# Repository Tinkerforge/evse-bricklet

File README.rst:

EVSE Bricklet
=============

This Bricklet together with the ESP32 Brick the NFC Bricklet and the
RS485 Bricklet form the hardware used in the WARP Charger.

See https://www.warp-charger.com/warp1.html for more details.

This repository contains the firmware source code and the hardware design
files. The documentation generator configs can be found at
https://github.com/Tinkerforge/generators

.. BEGIN WARP REPOSITORIES (managed block, generated from esp32-firmware/repo_overview.rst - do not edit by hand, run update_repo_overview.py instead)

WARP Repositories
-----------------

This is an overview of all repositories that make up the WARP Charger and
WARP Energy Manager ecosystem.

Please report **any** issue concerning WARP hard- or software in the
`esp32-firmware`_ repository, no matter which repository it originates from.

Software
~~~~~~~~

- `esp32-firmware`_ - Source code of the ESP32 firmware shared between all WARP Chargers and Energy Managers

Libraries used by the firmware:

- `tfjson`_ - SAX style JSON serializer and deserializer
- `tfnetwork`_ - Modbus TCP server and client implementation
- `tfocpp`_ - OCPP 1.6 implementation
- `tftools`_ - Miscellaneous tools and helpers

Remote access:

- `esp32-remote-access`_ - Source code of the my.warp-charger.com remote access server

Documentation, tools and integrations:

- `warp-charger`_ - Source code of (docs.)warp-charger.com and the printed manual, released firmwares, datasheets and documents, as well as some tools and hardware design files
- `api.warp-charger.com`_ - Serves APIs that are used by WARP Chargers to obtain relevant public information like day ahead prices
- `vislog.warp-charger.com`_ - Visualizes WARP Charger logs and EVSE debug protocols
- `dbus-warp-charger`_ - Integrates WARP Chargers into a Victron Energy Venus OS device (e.g. Cerbo GX)

WARP Charger Hardware
~~~~~~~~~~~~~~~~~~~~~~

WARP4 Charger
"""""""""""""

*Current charger generation.*

- `warp-esp32-ethernet-v2-brick`_ - Hardware design files of the WARP ESP32 Ethernet Brick 2.0
- `warp-esp32-ethernet-v2-co-bricklet`_ - Firmware source code of the WARP ESP32 Ethernet 2.0 Co Bricklet (co-processor)
- `evse-v4-bricklet`_ - Hardware design files of the EVSE 4.0 Bricklet (firmware shared with the EVSE 2.0 Bricklet)
- `nfc-bricklet`_ - Firmware source code and hardware design files of the NFC Bricklet

WARP3 Charger
"""""""""""""

- `warp-esp32-ethernet-brick`_ - Hardware design files of the WARP ESP32 Ethernet Brick
- `evse-v3-bricklet`_ - Hardware design files of the EVSE 3.0 Bricklet (firmware shared with the EVSE 2.0 Bricklet)
- `nfc-bricklet`_ - Firmware source code and hardware design files of the NFC Bricklet

WARP2 Charger
"""""""""""""

- `esp32-ethernet-brick`_ - Hardware design files of the ESP32 Ethernet Brick
- `evse-v2-bricklet`_ - Firmware source code and hardware design files of the EVSE 2.0 Bricklet
- `nfc-bricklet`_ - Firmware source code and hardware design files of the NFC Bricklet

WARP1 Charger
"""""""""""""

- `esp32-brick`_ - Hardware design files of the ESP32 Brick
- `evse-bricklet`_ - Firmware source code and hardware design files of the EVSE Bricklet
- `rs485-bricklet`_ - Firmware source code and hardware design files of the RS485 Bricklet

WARP Energy Manager Hardware
~~~~~~~~~~~~~~~~~~~~~~~~~~~~~~

WARP Energy Manager 2.0
"""""""""""""""""""""""

*Current energy manager generation.*

- `esp32-ethernet-brick`_ - Hardware design files of the ESP32 Ethernet Brick
- `warp-energy-manager-v2-bricklet`_ - Firmware source code and hardware design files of the WARP Energy Manager 2.0 Bricklet
- `warp-front-panel-bricklet`_ - Firmware source code and hardware design files of the WARP Front Panel Bricklet

WARP Energy Manager 1.0
"""""""""""""""""""""""

- `esp32-ethernet-brick`_ - Hardware design files of the ESP32 Ethernet Brick
- `warp-energy-manager-bricklet`_ - Firmware source code and hardware design files of the WARP Energy Manager Bricklet

Forked/patched projects
~~~~~~~~~~~~~~~~~~~~~~~~~

- `arduino-esp32`_
- `esp32-arduino-libs`_
- `WireGuard-ESP32-Arduino`_

.. Link targets: One definition per repository, keep in sync with the lists above.

.. _esp32-firmware: https://github.com/Tinkerforge/esp32-firmware
.. _tfjson: https://github.com/Tinkerforge/tfjson
.. _tfnetwork: https://github.com/Tinkerforge/tfnetwork
.. _tfocpp: https://github.com/Tinkerforge/tfocpp
.. _tftools: https://github.com/Tinkerforge/tftools
.. _esp32-remote-access: https://github.com/Tinkerforge/esp32-remote-access
.. _warp-charger: https://github.com/Tinkerforge/warp-charger
.. _api.warp-charger.com: https://github.com/Tinkerforge/api.warp-charger.com
.. _vislog.warp-charger.com: https://github.com/Tinkerforge/vislog.warp-charger.com
.. _dbus-warp-charger: https://github.com/Tinkerforge/dbus-warp-charger
.. _warp-esp32-ethernet-v2-brick: https://github.com/Tinkerforge/warp-esp32-ethernet-v2-brick
.. _warp-esp32-ethernet-v2-co-bricklet: https://github.com/Tinkerforge/warp-esp32-ethernet-v2-co-bricklet
.. _evse-v4-bricklet: https://github.com/Tinkerforge/evse-v4-bricklet
.. _nfc-bricklet: https://github.com/Tinkerforge/nfc-bricklet
.. _warp-esp32-ethernet-brick: https://github.com/Tinkerforge/warp-esp32-ethernet-brick
.. _evse-v3-bricklet: https://github.com/Tinkerforge/evse-v3-bricklet
.. _esp32-ethernet-brick: https://github.com/Tinkerforge/esp32-ethernet-brick
.. _evse-v2-bricklet: https://github.com/Tinkerforge/evse-v2-bricklet
.. _esp32-brick: https://github.com/Tinkerforge/esp32-brick
.. _evse-bricklet: https://github.com/Tinkerforge/evse-bricklet
.. _rs485-bricklet: https://github.com/Tinkerforge/rs485-bricklet
.. _warp-energy-manager-v2-bricklet: https://github.com/Tinkerforge/warp-energy-manager-v2-bricklet
.. _warp-front-panel-bricklet: https://github.com/Tinkerforge/warp-front-panel-bricklet
.. _warp-energy-manager-bricklet: https://github.com/Tinkerforge/warp-energy-manager-bricklet
.. _arduino-esp32: https://github.com/Tinkerforge/arduino-esp32
.. _esp32-arduino-libs: https://github.com/Tinkerforge/esp32-arduino-libs
.. _WireGuard-ESP32-Arduino: https://github.com/Tinkerforge/WireGuard-ESP32-Arduino

.. END WARP REPOSITORIES

Repository Content
------------------

software/:
 * examples/: Examples for all supported languages
 * build/: Compiled files
 * src/: Source code of firmware
 * Makefile: Makefile to build project

hardware/:
 * Contains KiCad project files and additionally schematics as PDF

datasheets/:
 * Contains datasheets for sensors and complex ICs that are used

Hardware
--------

The hardware is designed with the open source EDA Suite KiCad
(http://www.kicad.org). Before you are able to open the files,
you have to install the Tinkerforge kicad-libraries
(https://github.com/Tinkerforge/kicad-libraries). You can either clone
them directly in hardware/ or clone them in a separate folder and
symlink them into hardware/
(ln -s kicad_path/kicad-libraries project_path/hardware). After that you
can open the .pro file in hardware/ with KiCad and from there view and
modify the schematics and the PCB layout.

Software
--------

If you want to do your own Brick/Bricklet firmware development we highly
recommend that you use our build environment setup script and read the
tutorial (https://www.tinkerforge.com/en/doc/Tutorials/Tutorial_Build_Environment/Tutorial.html).

To compile the C code we recommend you to install the newest GNU Arm Embedded
Toolchain (https://launchpad.net/gcc-arm-embedded/+download).
You also need to install bricklib2 (https://github.com/Tinkerforge/bricklib2).

You can either clone it directly in software/src/ or clone it in a
separate folder and symlink it into software/src/
(ln -s bricklib_path/bricklib2 project_path/software/src/). Finally make sure to
have CMake installed (http://www.cmake.org/cmake/resources/software.html).

After that you can build the firmware by invoking make in software/.
The firmware (.zbin) can then be found in software/build/ and uploaded
with brickv (click button "Flashing" on start screen).

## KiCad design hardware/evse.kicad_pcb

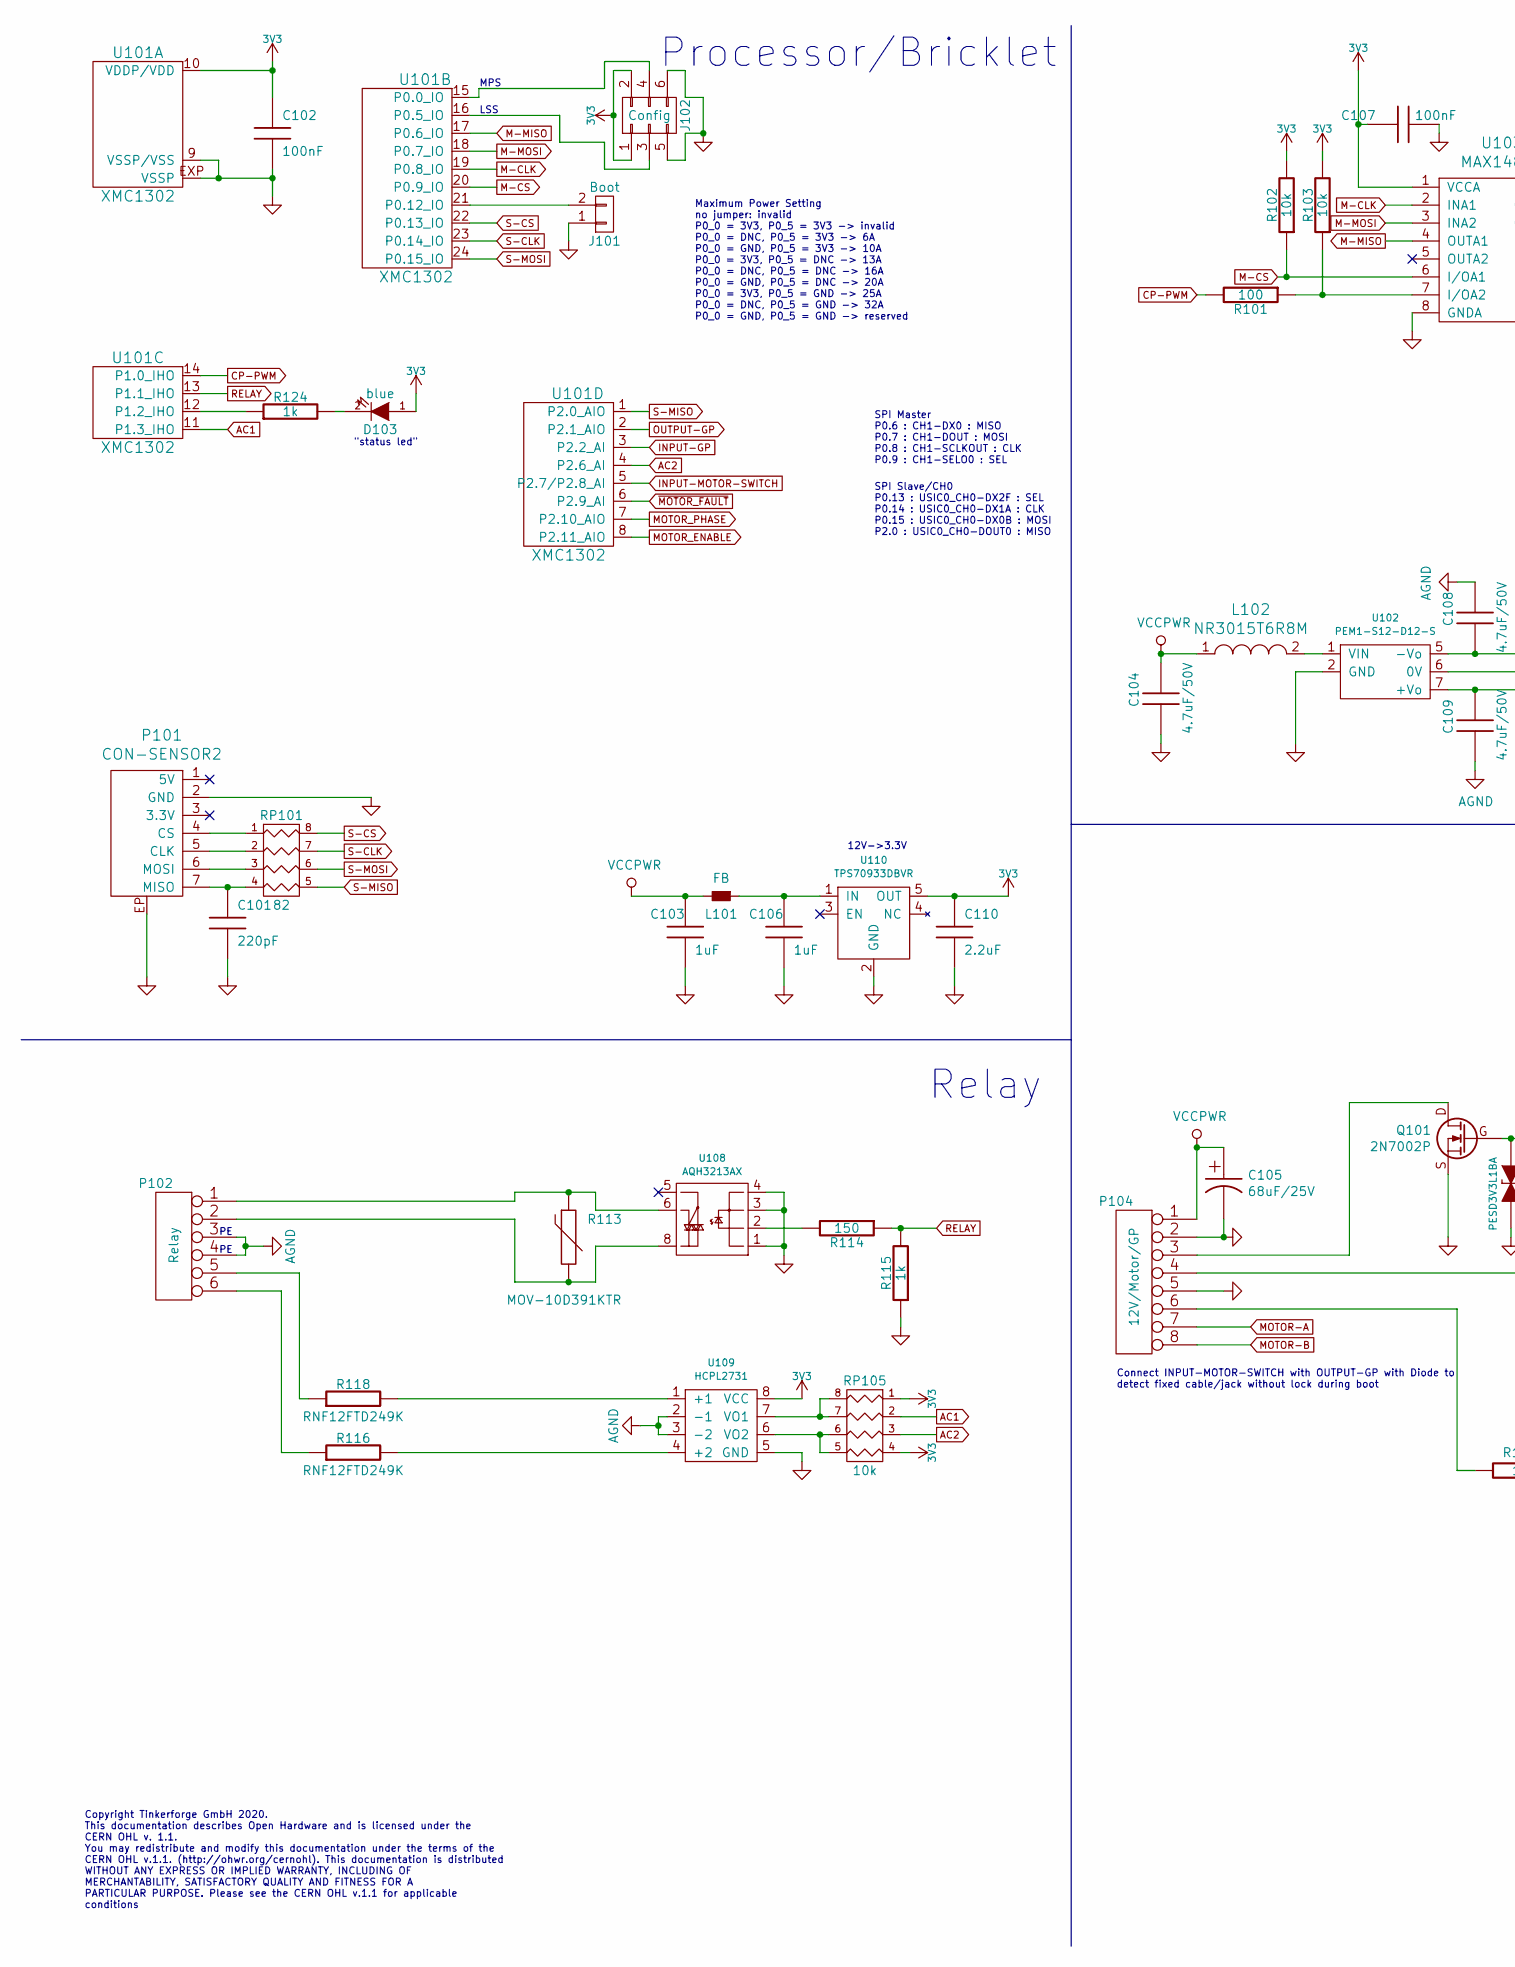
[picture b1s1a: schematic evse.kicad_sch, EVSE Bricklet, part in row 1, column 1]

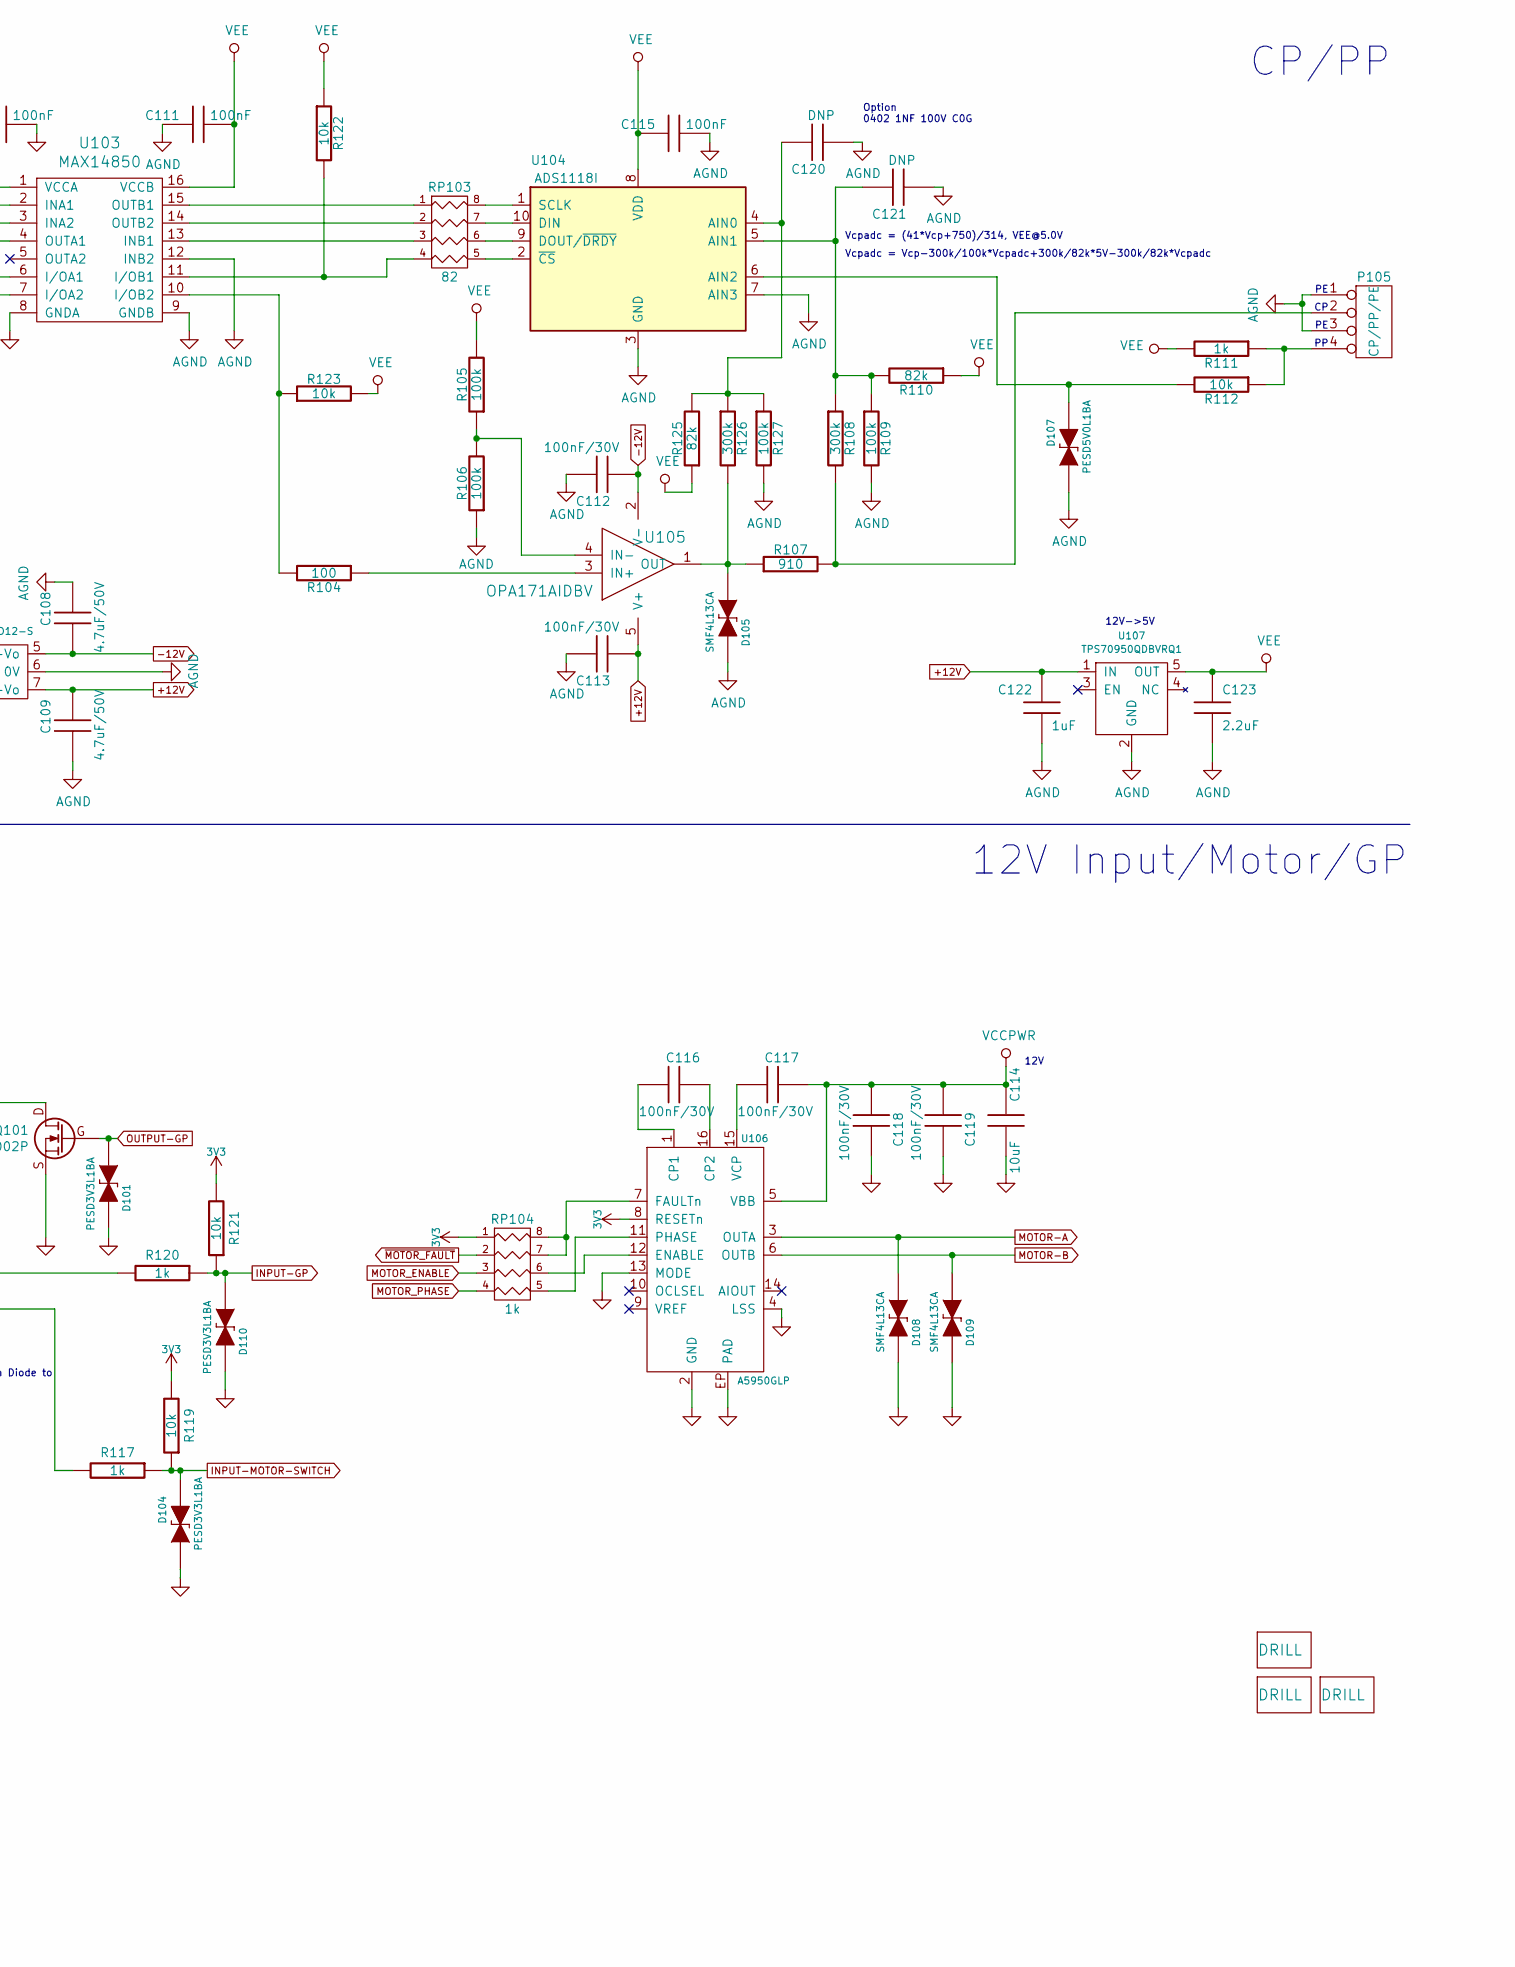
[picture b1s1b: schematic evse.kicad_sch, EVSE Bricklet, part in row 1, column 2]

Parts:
A101, A102, A103: DRILL; DRILL_NP
C101: 220pF; C0402F
C102, C107, C111, C115: 100nF; C0603F
C103, C106, C122: 1uF; C0603F
C104, C108, C109: 4.7uF/50V; C1206
C105: 68uF/25V; ELKO_63
C110, C123: 2.2uF; C0603F
C112, C113, C116, C117, C118, C119: 100nF/30V; C0603F
C114: 10uF; C1206
C120, C121: DNP; C0402F
D101, D104, D110: ‎PESD3V3L1BA; SOD-323
D103: blue; D0603F
D105, D108, D109: SMF4L13CA; SOD-123FL
D107: ‎PESD5V0L1BA; SOD-323
J101: Boot; SolderJumper
J102: Config; Pin_Header_Straight_2x03_127
L101: FB; R0603F
L102: NR3015T6R8M; NR3030
P101: CON-SENSOR2; CON-SENSOR2_180
P102: Relay; OQ_6P_Vertical
P104: 12V/Motor/GP; OQ_8P_Vertical
P105: CP/PP/PE; OQ_4P_Vertical
Q101: 2N7002P; SOT23GDS
R101, R104: 100; R0603F
R102, R103, R112, R119, R121, R122, R123: 10k; R0603F
R105, R106, R109, R127: 100k; R0603F
R107: 910; R0603F
R108, R126: 300k; R0603F
R110, R125: 82k; R0603F
R111, R115, R117, R120, R124: 1k; R0603F
R113: MOV-10D391KTR; VAR_10mm
R114: 150; R0603F
R116, R118: RNF12FTD249K; RNF12
RP101, RP103: 82; 4X0402
RP104: 1k; 4X0603
RP105: 10k; 4X0603
U101: XMC1302; QFN24-4x4mm-0.5mm
U102: PEM1-S12-D12-S; PEM1S
U103: MAX14850; SOIC16
U104: ADS1118I; VSSOP10
U105: OPA171AIDBV; SOT23-5
U106: A5950GLP; TSSOP16_EP
U107: TPS70950QDBVRQ1; SOT23-5
U108: AQH3213AX; AQ-H
U109: HCPL2731; DIP-8
U110: TPS70933DBVR; SOT23-5

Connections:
3V3: C102.1, C107.1, C110.1, D103.1 (A), J102.1, J102.2, R102.2, R103.2, R119.2, R121.2, RP104.1, RP105.1, RP105.4, U101.10 (VDDP/VDD), U103.1 (VCCA), U106.8 (RESETn), U109.8 (VCC), U110.5 (OUT)
+12V: C109.1, C113.2, C122.1, U102.7 (+Vo), U105.5 (V+), U107.1 (IN)
-12V: C108.2, C112.2, U102.5 (-Vo), U105.2 (V-)
AC1: RP105.2, U101.11 (P1.3_IHO)
AC2: RP105.3, U101.4 (P2.6_AI)
AGND: C108.1, C109.2, C111.1, C112.1, C113.1, C115.2, C120.2, C121.2, C122.2, C123.2, D105.2 (K), D107.1 (A), P102.3, P102.4, P105.1, P105.3, R106.1, R109.2, R127.2, U102.6 (0V), U103.9 (GNDB), U103.12 (INB2), U104.3 (GND), U104.7 (AIN3), U107.2 (GND), U109.2 (-1), U109.3 (-2)
CP-PWM: R101.2, U101.14 (P1.0_IHO)
GND: C101.2, C102.2, C103.2, C104.2, C105.2, C106.2, C107.2, C110.2, C114.2, C118.1, C119.1, D101.2 (K), D104.1 (A), D108.2 (K), D109.2 (K), D110.2 (K), J101.1, J102.5, J102.6, P101.2 (GND), P101.EP, P104.2, P104.5, Q101.S, R115.1, U101.9 (VSSP/VSS), U101.EXP (VSSP), U102.2 (GND), U103.8 (GNDA), U106.2 (GND), U106.4 (LSS), U106.13 (MODE), U106.EP (PAD), U108.1, U108.3, U108.4, U109.5 (GND), U110.2 (GND)
INPUT-GP: D110.1 (A), R120.1, R121.1, U101.3 (P2.2_AI)
INPUT-MOTOR-SWITCH: D104.2 (K), R117.1, R119.1, U101.5 (P2.7/P2.8_AI)
M-CLK: U101.19 (P0.8_IO), U103.2 (INA1)
M-CS: R102.1, U101.20 (P0.9_IO), U103.6 (I/OA1)
M-MISO: U101.17 (P0.6_IO), U103.4 (OUTA1)
M-MOSI: U101.18 (P0.7_IO), U103.3 (INA2)
MOTOR-A: D108.1 (A), P104.7, U106.3 (OUTA)
MOTOR-B: D109.1 (A), P104.8, U106.6 (OUTB)
MOTOR_ENABLE: RP104.3, U101.8 (P2.11_AIO)
MOTOR_PHASE: RP104.4, U101.7 (P2.10_AIO)
unnamed: C101.1, P101.7 (MISO), RP101.4
unnamed: C106.1, L101.1, U110.1 (IN)
unnamed: C116.1, U106.16 (CP2)
unnamed: C116.2, U106.1 (CP1)
unnamed: C117.2, U106.15 (VCP)
unnamed: C120.1, R125.2, R126.1, R127.1, U104.4 (AIN0)
unnamed: C121.1, R108.1, R109.1, R110.2, U104.5 (AIN1)
unnamed: D103.2 (K), R124.2
unnamed: D105.1 (A), R107.1, R126.2, U105.1 (OUT)
unnamed: D107.2 (K), R112.2, U104.6 (AIN2)
unnamed: J101.2, U101.21 (P0.12_IO)
unnamed: J102.3, U101.16 (P0.5_IO)
unnamed: J102.4, U101.15 (P0.0_IO)
unnamed: L102.2, U102.1 (VIN)
unnamed: P101.4 (CS), RP101.1
unnamed: P101.5 (CLK), RP101.2
unnamed: P101.6 (MOSI), RP101.3
unnamed: P102.1, R113.1, U108.6
unnamed: P102.2, R113.2, U108.8
unnamed: P102.5, R118.1
unnamed: P102.6, R116.1
unnamed: P104.3, Q101.D
unnamed: P104.4, R120.2
unnamed: P104.6, R117.2
unnamed: P105.2, R107.2, R108.2
unnamed: P105.4, R111.1, R112.1
unnamed: R101.1, R103.1, U103.7 (I/OA2)
unnamed: R104.1, U105.3 (IN+)
unnamed: R104.2, R123.1, U103.10 (I/OB2)
unnamed: R105.1, R106.2, U105.4 (IN-)
unnamed: R114.2, U108.2
unnamed: R116.2, U109.4 (+2)
unnamed: R118.2, U109.1 (+1)
unnamed: R122.2, RP103.4, U103.11 (I/OB1)
unnamed: R124.1, U101.12 (P1.2_IHO)
unnamed: RP103.1, U103.15 (OUTB1)
unnamed: RP103.2, U103.14 (OUTB2)
unnamed: RP103.3, U103.13 (INB1)
unnamed: RP103.5 (R4), U104.2 (~CS)
unnamed: RP103.6 (R3), U104.9 (DOUT/~DRDY)
unnamed: RP103.7 (R2), U104.10 (DIN)
unnamed: RP103.8 (R1), U104.1 (SCLK)
unnamed: RP104.5 (R4), U106.11 (PHASE)
unnamed: RP104.6 (R3), U106.12 (ENABLE)
unnamed: RP104.7 (R2), RP104.8 (R1), U106.7 (FAULTn)
unnamed: RP105.5 (R4), RP105.6 (R3), U109.6 (VO2)
unnamed: RP105.7 (R2), RP105.8 (R1), U109.7 (VO1)
OUTPUT-GP: D101.1 (A), Q101.G, U101.2 (P2.1_AIO)
RELAY: R114.1, R115.2, U101.13 (P1.1_IHO)
S-CLK: RP101.7 (R2), U101.23 (P0.14_IO)
S-CS: RP101.8 (R1), U101.22 (P0.13_IO)
S-MISO: RP101.5 (R4), U101.1 (P2.0_AIO)
S-MOSI: RP101.6 (R3), U101.24 (P0.15_IO)
VCC: C103.1, C104.1, C105.1, C114.1, C117.1, C118.2, C119.2, L101.2, L102.1, P104.1, U106.5 (VBB)
VEE: C111.2, C115.1, C123.1, R105.2, R110.1, R111.2, R122.1, R123.2, R125.1, U103.16 (VCCB), U104.8 (VDD), U107.5 (OUT)
~MOTOR_FAULT: RP104.2, U101.6 (P2.9_AI)

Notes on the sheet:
Relay
Vcpadc = Vcp-300k/100k*Vcpadc+300k/82k*5V-300k/82k*Vcpadc
12V
Processor/Bricklet
LSS
"status led"
SPI Slave/CH0 P0.13 : USIC0_CH0-DX2F : SEL P0.14 : USIC0_CH0-DX1A : CLK P0.15 : USIC0_CH0-DX0B : MOSI P2.0 : USIC0_CH0-DOUT0 : MISO
Maximum Power Setting no jumper: invalid P0_0 = 3V3, P0_5 = 3V3 -> invalid P0_0 = DNC, P0_5 = 3V3 -> 6A P0_0 = GND, P0_5 = 3V3 -> 10A P0_0 = 3V3, P0_5 = DNC -> 13A P0_0 = DNC, P0_5 = DNC -> 16A P0_0 = GND, P0_5 = DNC -> 20A P0_0 = 3V3, P0_5 = GND -> 25A P0_0 = DNC, P0_5 = GND -> 32A P0_0 = GND, P0_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
CP/PP
MPS
12V Input/Motor/GP
Option 0402 1NF 100V C0G
12V->5V
Copyright Tinkerforge GmbH 2020. This documentation describes Open Hardware and is licensed under the CERN OHL v. 1.1. You may redistribute and modify this documentation under the terms of the CERN OHL v.1.1. (http://ohwr.org/cernohl). This documentation is distributed WITHOUT ANY EXPRESS OR IMPLIE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
Connect INPUT-MOTOR-SWITCH with OUTPUT-GP with Diode to detect fixed cable/jack without lock during boot
12V->3.3V
Vcpadc = (41*Vcp+750)/314, VEE@5.0V
SPI Master P0.6 : CH1-DX0 : MISO P0.7 : CH1-DOUT : MOSI P0.8 : CH1-SCLKOUT : CLK P0.9 : CH1-SELO0 : SEL

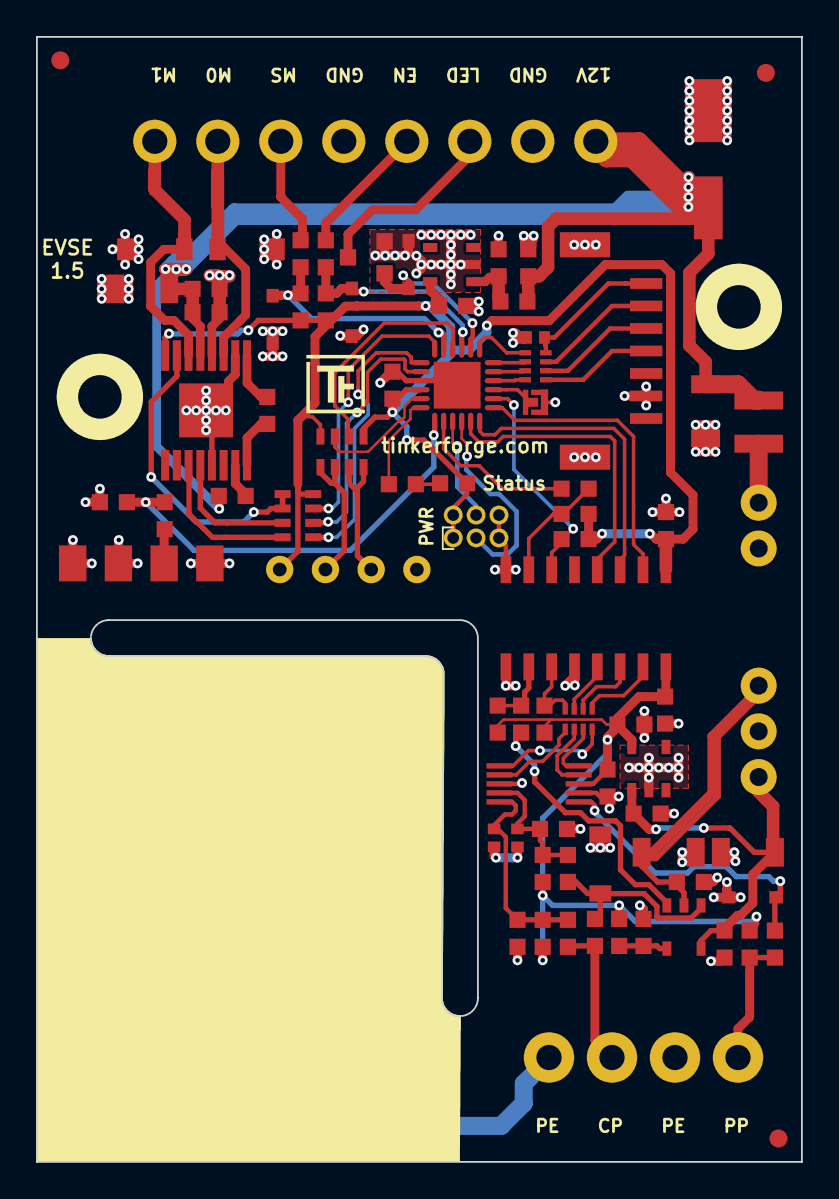
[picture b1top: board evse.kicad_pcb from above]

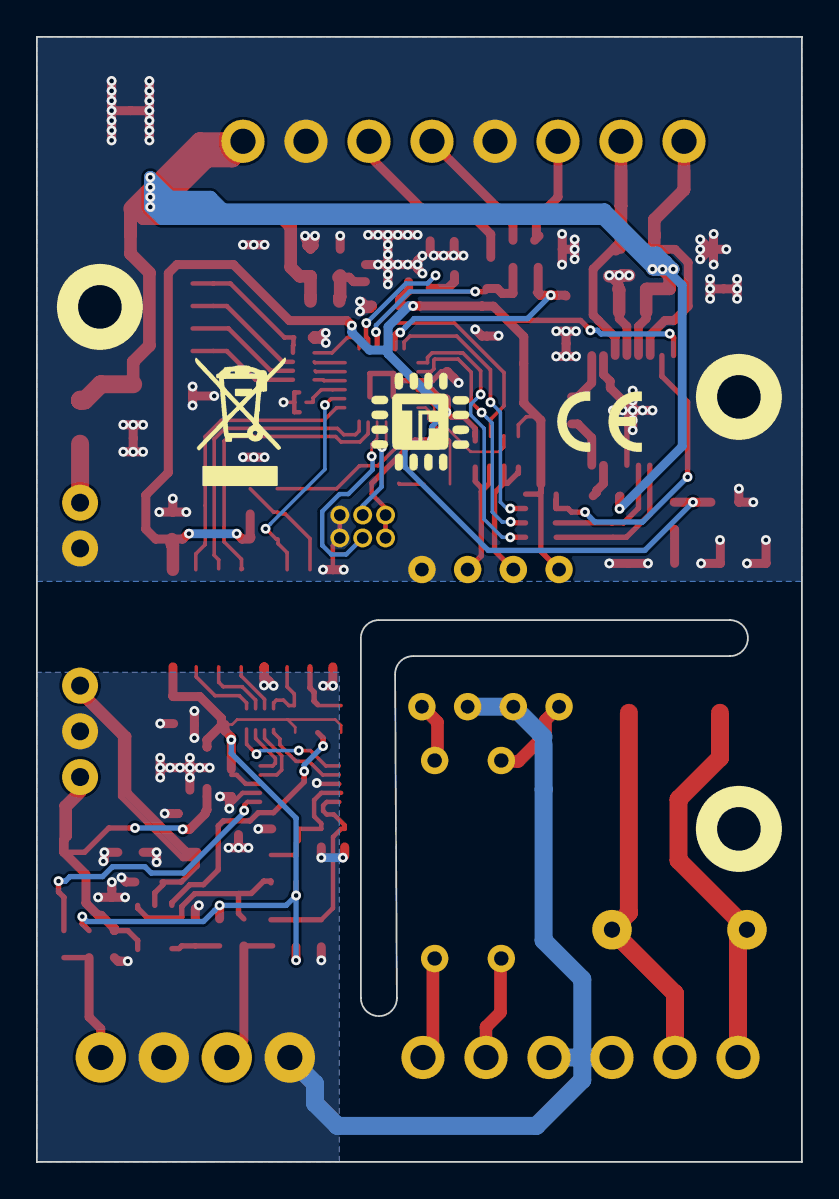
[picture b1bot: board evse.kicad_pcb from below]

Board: 2 copper layers, 42.5 x 62.5 mm, 90 parts (2 on the bottom side), 74 nets.

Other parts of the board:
Fiducial_Mark: VAL**; Fiducial_Mark
Fiducial_Mark#2, Fiducial_Mark#3, Fiducial_Mark#4: VAL**; Fiducial_Mark
VAL: CE_5mm
VAL#2: WEEE_7mm

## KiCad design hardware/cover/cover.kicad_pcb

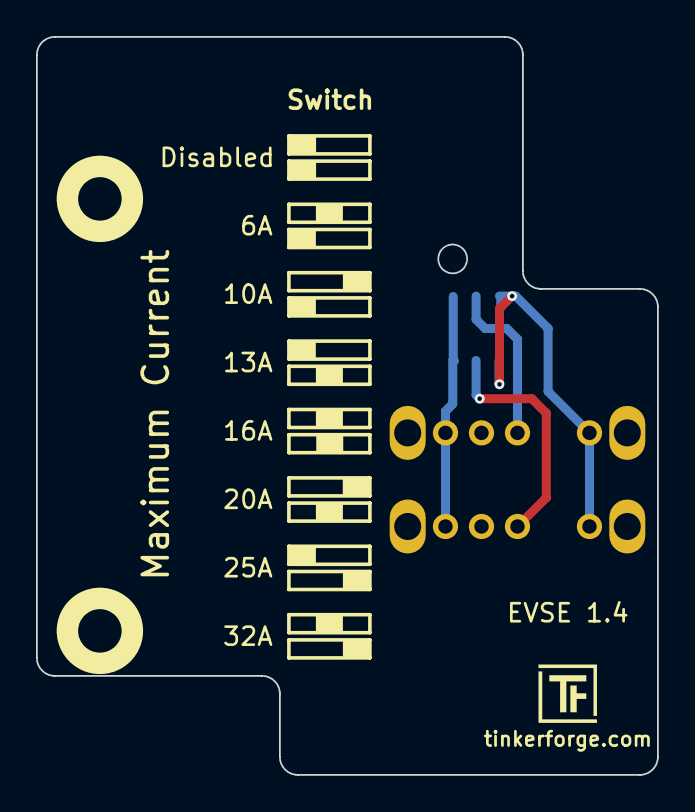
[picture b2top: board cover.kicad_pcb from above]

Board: 2 copper layers, 34.5 x 41.0 mm, 5 parts (1 on the bottom side), 4 nets.

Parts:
A101, A103: DRILL; DRILL_NP
P101: CONN_02X03; Pin_Header_Straight_Female_2x03_127
SW101, SW102: OS103011MS8QP1

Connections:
3V3: P101.1, P101.2, SW101.4, SW102.4
GND: P101.5, P101.6, SW101.1, SW102.1
unnamed: P101.3, SW102.2
unnamed: P101.4, SW101.2

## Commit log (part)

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2020-03-31 init repository
2020-04-03 version 1.0
2020-04-03 specify 3.3V TVS Diodes
2020-04-06 ordered prototype
2020-04-06 start version 1.1
    * fix connector orientation (rotate by 180 degree)
2020-04-16 fix bottom logo positions
2020-04-16 fixed typo
2020-04-17 changed cap value
2020-04-20 Add initial test firmware
2020-04-21 specify resistor
2020-04-21 fix m-cs and pwm signal shift
2020-04-21 thermal improvement
2020-04-21 change p105 pinout, add description text
2020-04-21 change mounting hole positions
2020-04-21 change fiducial positons
2020-04-21 add some artwork, add missing pullup resistors for pwm and cs
2020-04-21 add pwm pin control
2020-04-21 small routing improvements
2020-04-22 fix tvs/zener diodes, fix pp description
2020-04-22 Add stub for ADS1118 16-Bit SPI ADC driver
2020-04-22 Add ADS1118 datasheet
2020-04-22 Fix typo
2020-04-22 fix led colors and description
2020-04-27 add version 1.2:
    remove error led
    add maximum power jumper
2020-04-29 change to xmc1302
2020-04-30 add version 1.3
    * add external output for led control
    * remove internal charge led
    * add cutout
    * change pin mappings
    * change pin silkscreen text
2020-05-12 Add initial iec61851 support
2020-05-15 Update pinout to new hardware version, improve debug
2020-05-19 Add A5950 datasheet
2020-05-19 start version 1.4, change configuration header
2020-05-19 change current setting documentation
2020-05-19 ordered version
2020-05-20 Add support for LED, button and jumper configuration
2020-05-29 Add moving average to voltage measurements
2020-07-08 Add support for uptime
2020-07-08 Add uptime for state to tests
2020-07-09 Use UINT32_T for moving average and a max resistance of 0xFFFF
    With this we have enough room to do the moving average without overflow
2020-08-10 Button logic changed from active high to active low
2020-09-25 Save last state change
2020-09-25 Activate jumper initialization
2020-09-25 Split get_state into get_state, get_hardware_configuration and get_low_level_state
2020-09-25 Add calibration API
    TODO: Actual calibration still missing
2020-09-28 Use bool for motor direction
2020-09-29 add formula
2020-09-29 Add min/max CP/PE voltage calibration
2020-10-06 Add continuous calibration support
2020-10-07 mark diode as DNP
2020-10-09 Implement new calibration method
    We now calibrate the "max voltage" as well as the
    offset to the absolute value of the "min voltage"
    by external measurements.
    This makes the resistance measurement very precise now
    (maximum error of +-1.5% now in my tests).
2020-10-14 updated vertical OQ connectors with new F.Fab layer
2020-10-14 Update API
2020-10-14 Remove low level mode for now
2020-10-15 add cover pcb
2020-10-26 decrease outline dimensions
2020-10-30 Add LED error states
2020-10-30 Add EVSETester and EVSETester tests
2020-10-30 Handle LED state changes when button was pressed properly
2020-11-05 change cover to two single switch design, change current setting!!!!
2020-11-16 adapt jumper settings for new cover PCB
2020-11-16 fix comments
2020-11-18 Add startup/calibration flicker state
2020-12-03 Switch between normal loop and fast loop depending on IEC61851 state.
    When we are in state C, the standard says that we have to turn the
    contactor off within at most 100ms!
    With the normal loop we have an ADC integration time of 250ms, so we
    can't possibly react fast enough.
    To fix this we have a "fast loop" that is used in state C.
    The fast loop measures with an integration time of TBDms and it only
2020-12-03 Add integration time
2020-12-16 Use 32SPS for fast mode instead of 128SPS
    This is still fast enough to satisfy the 100ms defined in the IEC61851
    standard, but there is much less noise in the ADC data
2020-12-16 Use 300 ohm as lower range for state C
2020-12-16 Only turn ignore the LED pin if logging is enabled
    We run the rest of the code normally to make sure that
    everything behaves exactly the same if logging is enabled
2020-12-16 Add support for start/stop charging aut set/get autostart
2020-12-16 Add support for autostart
2020-12-16 Add vehicle state to get state function
2020-12-17 Remove motor direction and duty cycle
    Too low-level for a user
2020-12-22 Make sure changing autostart to false works immediately with next charing cycle
2020-12-23 We use resistance divider of 910 ohm on EVSE
2020-12-23 Fix comment
2020-12-23 User better calibration default
2021-01-05 Add real-world test comment
2021-01-11 Fix typos
2021-01-11 Never return true if autostart is disabled
2021-01-11 Add custom log function to tester
2021-01-11 Update bindings
2021-01-11 Add full test
2021-01-11 Add full_test_log.csv value logging
2021-01-15 Add calibration for different duty cycles in state C
2021-01-15 Use differen Industrial Digital Out 4
2021-01-27 Make sure 2700ohm and 880ohm calibration is not overwritten by initial memset
2021-01-27 Add error states (corresponds to LED blink codes)
2021-01-27 Increase revision
2021-01-29 Add TODO for iec61851_get_ma_from_pp_resistance
2021-02-01 Remove Zoe Test
    The test was done before the calibration with different charging
    currents. With the calibration the resistance is always around 880 Ohm,
    as expected.
2021-02-08 Make sure start_charging does nothing if autostart is disabled and no car is connected
2021-02-08 Add ref for v2.0.2
2021-02-16 Update default cal_min/max_voltage
    We take the average min/max voltage of the first 100 calibrated EVSEs.
    This default value should now be as good as it gets.
2021-02-16 Allow connected car during initial calibration
    we just need to make sure to not activate the contactor
2021-02-16 Add 2.0.3 rev
2021-02-16 Make sure initial value for contactor check is correct
2021-02-16 spaces -> tabs
2021-02-16 Add ref for 2.0.4
2021-03-08 Add charge release support to GetState API
2021-03-08 Check error state first
2021-03-08 Bump version to 2.0.5 and add changelog
2021-05-07 Add managed support
2021-05-07 Make sure managed current doesn't go back and forth between 32000 and 0 in unmanaged state
2021-05-07 If we are managed and managed currenet is 0, we don't go to state C
2021-05-10 add version 1.5
2021-05-10 Add support for hardware version 1.5
2021-05-10 Remove EVSE lock switch support for now
    This is not used by WARP charger and EVSE hardware 1.x will not be sold
    to any third party, we will start third party sales with 2.x
2021-05-10 Remove lock tick and other unused lock code
2021-05-10 Start with find version configuration
2021-05-10 Invalidate the next measurement on both channels after version detection
2021-05-10 Bump version to 2.0.6 and add changelog entry
2021-05-10 Add rev for v2.0.6
2021-05-25 Add user calibration support
2021-05-25 Save user calibration after setter call
2021-05-28 Add special handling for ID.3 behavior
    When an ID.3 is connected to the WARP charger and the duty cycle is already
    below 100% (the wallbox is ready) but the contactor is not yet activated, the
    ID.3 somtimes generates a spike in the resistance that we measure when it
    engages the resistor to apply 880 ohm between CP/PE. We have not seen this in
    other cars, we assume this is some kind of capacitive effect. To make sure
    that we don't cancel the charging here, we increase the "STATE A" threshold and
2021-05-28 sort "magic" and "active" position the other way around
2021-05-28 Save active state before ADS1118 struct memset to 0
2021-05-28 Fix log statements
2021-05-28 Add proper constants
2021-05-28 Save EVSE configuration in EEPROM to make it persistant after restart
    Currently we only save the managed configuration
2021-06-08 Update changelog
2021-06-08 Add ref for 2.0.7
2021-07-06 Remove typo
2021-07-06 Add evse_get_cp_duty_cycle and evse_set_cp_duty_cycle function
    This fixes accidental erroneous initialization of cp_duty_cycle
2021-07-06 Add ref for 2.0.8
2021-07-06 Use the correct magic number for managed configuration
2021-07-06 Fix ref for 2.0.8
2021-07-06 Ignore glitches in contactor check
2021-07-06 Add ref for 2.0.9
2021-07-16 Add hardware version to get_low_level_state
2021-07-16 Add ref for v2.0.10
2021-07-21 Add data storage
2021-10-05 Add set_indicator_led API (compatible to EVSE V2)
2021-10-11 Add 500ms delay between state change from B to A in ID.3 mode
2021-10-11 Add rev for 2.0.11
2021-10-12 Add TimeSinceCPPWMChange parameter to low level state getter
2021-10-12 Calculate time since pwm change correctly
2021-10-12 Only update pwm time if we change from or to 100%
2021-10-13 Add ChargeTime parameter to low level state getter
2021-10-15 Add GetAllDataX API
    For internal use in WARP Charger only
2021-10-20 Set charging time to 0 if in managed mode and max current is changed to 0
2021-10-25 Update KiCad link
    https://www.kicad.org/blog/2021/10/Avoid-links-to-former-kicad-domain/
2021-10-27 Add date and rev for 2.0.12
2022-03-04 Add charging slot support
    This is made to be as close to the EVSE V2 implementation as possible
    to make sure that it behaves the same.
2022-03-07 Add missing button_pressed value in AllData function
2022-03-07 Make sure button charging slots allowes charging again
2022-03-30 Add rev and release date for 2.1.0 to changelog
2022-05-02 Add FactoryReset-function
2022-05-02 Add ref for 2.1.1
2022-05-06 Improve button/key stop logic
2022-05-06 Add ref for 2.1.2
2022-06-07 * Make sure to never start charging when key switch is turned off
    * Increase ID.3 mode wait time hysteresis time from 500ms to 2500ms
    * Make sure LED turns on until standby for every state change
2022-06-07 Add ref for 2.1.3
2022-07-06 Add license files.
2022-07-29 Make sure charging starts again when autostart is active
    and stop button was pressed while car was not charging
2022-07-29 Improve CP/PE resistance calculation
    Make sure there can't be over-/underflow
2022-09-13 Add date and rev for firmware version 2.1.4
2022-11-16 Add additional master communication watchdog
2022-11-16 Update changelog ref and date
2022-12-22 Add API for get/set boost mode, make sure contactor is not turned off under load
2022-12-22 Add date and ref for 2.1.6
2023-03-23 README: Remove development hint, add some details
2023-06-15 Move contactor check to bricklib2/warp
2023-06-16 Add blink led indicator code 2001-2010 for custom error code
    with 1-10 "blink amount"
2023-06-21 Add date and ref for v2.1.7
2023-07-06 Fix read of stored startup value of boost mode
2023-07-06 Make sure that ID.3 mode also works for state changes that go from C directly to A
2023-07-07 Add additional hysteresis for contactor
2023-07-07 User has to disconnect first for error state EF, but not for D
2023-08-21 Add CONTACTOR_PIN define for bricklib2 compatibility
    Some changes of the WARP3 branch did leak into the bricklib2.
    For now we just use both defines here (RELAY and CONTACTOR).
    Later when we merge the WARP3 branch the RELAY define will be removed.
2023-08-21 Add rev and release date for v2.1.8
2023-08-22 Fix typo in changelog
2023-12-21 Make sure that it is not blocked by default if extern control is enabled
2023-12-21 Add changelog entry for 2.1.9 changes
2024-01-10 Remove jumper config double check
2024-01-10 Every error state results in a charger state
2024-01-23 Add date and ref for 2.1.9
2024-02-02 move to kicad 7
2024-06-12 fix whitespace
2024-06-27 Force 16A PWM in specific state for better CP/PE measurement
2024-07-24 Add changelog for 2.1.10
2024-09-05 Make sure charging time is zeroed when car does not wake up
2024-09-05 Update revision
2024-09-18 Add ref for 2.1.11
2024-09-19 Make sure charging time is always started when IEC61851 state changes to C
2024-09-19 Add ref for 2.1.12
2024-11-18 Fix whitespace
    Normally the Bricklet firmwares use tabs. Lots of spaces have
    crept into the EVSE firmware, convert it back to tabs.
2024-12-03 Remove "charging time" and add "car stopped charging"
2024-12-05 Set external charging slot to enabled with 32A on first boot of 2.1.13
2024-12-05 Add date and rev for 2.1.13
2025-09-21 Make cmake version compatible to new build environment
2025-09-21 Always define LOGGING_UARTBB for CoMCU-Bricklets
    otherwise the compiler sees a rogue "printf" because of
    #ifdefs and throws bogus warnings

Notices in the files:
hardware/cover/cover.kicad_pcb:
Licensed under CERN OHL v.1.1
Copyright (©) 2020, B.Nordmeyer
